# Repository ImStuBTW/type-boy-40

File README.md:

# The Type Boy 40

This keyboard is a test bed for the revised TyepPak Advance microcontroller breakout board. It's a relatively simple 4x12 ortholinear keyboard.

## Features

- TypePak Advance cartridge slot
- VIK expansion port (Bottom mount, requires Type-B FPC cable.)
- Per-key SK6812Mini-E RGB LEDs
- Mid-Mount USB-C port
- Power switch
- Reset button

## Current Status

This board hasn't been built yet. Fab at your own risk!

## BOM

TBD

## Footprint Credits

- `diode-rear` is a variant of the stock Ergogen footprint which only has SMD pads on the rear.
- `esd` is a converted `SOT-23-6_Handsoldering` footprint from KiCAD's stock libraries.
- `fff_logo` is a logo I made. Features SMD pads as glasses.
- `gba` is a converted version of the DS Lite cartridge print from HDR's [Game-Boy-KiCAD-Library](https://github.com/HDR/Game-Boy-KiCad-Library) library.
- `jumper` is a converted KiCAD footprint.
- `led_sk6812mini-e` is from ceoloide's [ergogen-footprints](https://github.com/ceoloide/ergogen-footprints) library.
- `m2mountinghole` is converted from KiCAD.
- `power` is the stock Ergogen slide switch with Pad 3 exposed to allow you to specify which direction of the switch is "on".
- `smd805` is a converted KiCAD hand soldered 805 SMD component footprint.
- `usbcmid` is converted from Keeb.io's [Keebio-Parts.pretty](https://github.com/keebio/Keebio-Parts.pretty) library.
- `vik_cutout` is something I threw together in about 4 minutes.
- `vik_horizontal` and `vik_logo` come from sadekbaroudi's excellent [VIK](https://github.com/sadekbaroudi/vik) keyboard extension standard. Go Fingerpunch!

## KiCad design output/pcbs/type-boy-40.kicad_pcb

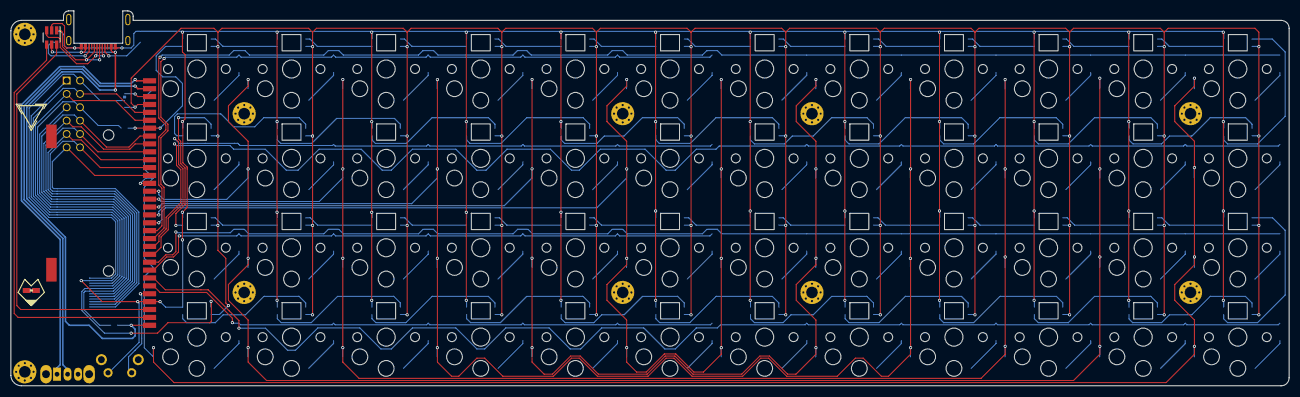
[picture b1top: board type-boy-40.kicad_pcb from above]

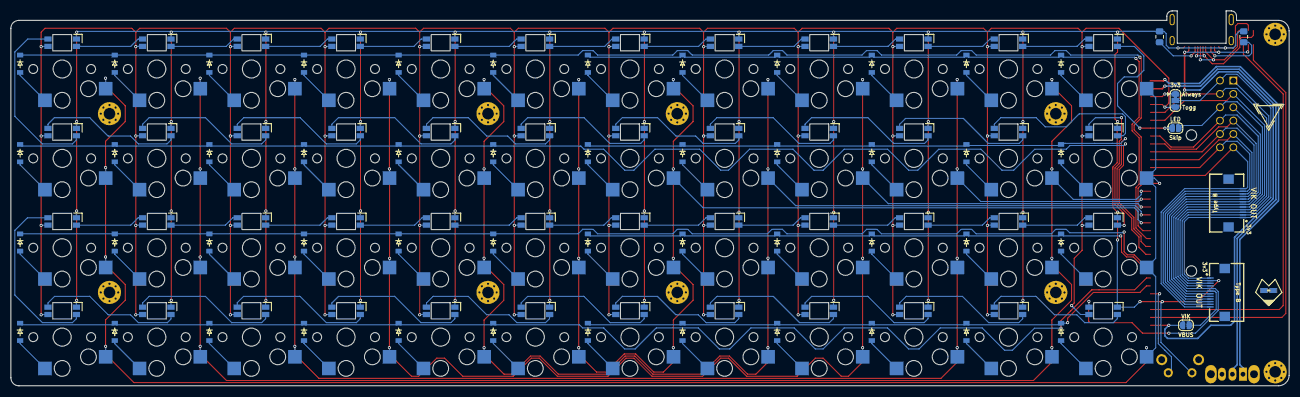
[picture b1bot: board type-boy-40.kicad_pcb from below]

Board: 2 copper layers, 243.1 x 71.3 mm, 161 parts (53 on the bottom side), 122 nets.

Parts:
D1, D2, D3, D4, D5, D6, D7, D8, D9, D10, D11, D12, D13, D14, D15, D16, D17, D18, D19, D20, D21, D22, D23, D24, D25, D26, D27, D28, D29, D30, D31, D32, D33, D34, D35, D36, D37, D38, D39, D40, D41, D42, D43, D44, D45, D46, D47, D48: ComboDiode
LED1, LED2, LED3, LED4, LED5, LED6, LED7, LED8, LED9, LED10, LED11, LED12, LED13, LED14, LED15, LED16, LED17, LED18, LED19, LED20, LED21, LED22, LED23, LED24, LED25, LED26, LED27, LED28, LED29, LED30, LED31, LED32, LED33, LED34, LED35, LED36, LED37, LED38, LED39, LED40, LED41, LED42, LED43, LED44, LED45, LED46, LED47, LED48: led_SK6812mini-e (per-keysingle-side)
S1, S2, S3, S4, S5, S6, S7, S8, S9, S10, S11, S12, S13, S14, S15, S16, S17, S18, S19, S20, S21, S22, S23, S24, S25, S26, S27, S28, S29, S30, S31, S32, S33, S34, S35, S36, S37, S38, S39, S40, S41, S42, S43, S44, S45, S46, S47, S48: PG1350
TH1: vik-keyboard-throughole
VIK OUT: vik-keyboard-connector-horizontal
XX1: vik-keyboard-connector-horizontal
XX3: SolderJumper-3_default.3mm_Bridged12_RoundedPad1.0x1.5mm
XX4: SolderJumper-2_from.3mm_Open_RoundedPad1.0x1.5mm
XX6, XX8: Untitled
_1, _2, _3, _4, _5, _6, _7, _8, _9, _10: MountingHole_2.2mm_M2_Pad_Via

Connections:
GND: LED1.3, LED2.3, LED3.3, LED4.3, LED5.3, LED6.3, LED7.3, LED8.3, LED9.3, LED10.3, LED11.3, LED12.3, LED13.3, LED14.3, LED15.3, LED16.3, LED17.3, LED18.3, LED19.3, LED20.3, LED21.3, LED22.3, LED23.3, LED24.3, LED25.3, LED26.3, LED27.3, LED28.3, LED29.3, LED30.3, LED31.3, LED32.3, LED33.3, LED34.3, LED35.3, LED36.3, LED37.3, LED38.3, LED39.3, LED40.3, LED41.3, LED42.3, LED43.3, LED44.3, LED45.3, LED46.3, LED47.3, LED48.3, TH1.2, VIK OUT.2, XX1.2
LED1: LED4.2, LED8.4
LED2: LED8.2, LED12.4
LED3: LED12.2, LED16.4
LED4: LED16.2, LED20.4
LED5: LED20.2, LED24.4
LED6: LED24.2, LED28.4
LED7: LED28.2, LED32.4
LED8: LED32.2, LED36.4
LED9: LED36.2, LED40.4
LED10: LED40.2, LED44.4
LED11: LED44.2, LED48.4
LED12: LED47.4, LED48.2
LED13: LED43.4, LED47.2
LED14: LED39.4, LED43.2
LED15: LED35.4, LED39.2
LED16: LED31.4, LED35.2
LED17: LED27.4, LED31.2
LED18: LED23.4, LED27.2
LED19: LED19.4, LED23.2
LED20: LED15.4, LED19.2
LED21: LED11.4, LED15.2
LED22: LED7.4, LED11.2
LED23: LED3.4, LED7.2
LED24: LED2.4, LED3.2
LED25: LED2.2, LED6.4
LED26: LED6.2, LED10.4
LED27: LED10.2, LED14.4
LED28: LED14.2, LED18.4
LED29: LED18.2, LED22.4
LED30: LED22.2, LED26.4
LED31: LED26.2, LED30.4
LED32: LED30.2, LED34.4
LED33: LED34.2, LED38.4
LED34: LED38.2, LED42.4
LED35: LED42.2, LED46.4
LED36: LED45.4, LED46.2
LED37: LED41.4, LED45.2
LED38: LED37.4, LED41.2
LED39: LED33.4, LED37.2
LED40: LED29.4, LED33.2
LED41: LED25.4, LED29.2
LED42: LED21.4, LED25.2
LED43: LED17.4, LED21.2
LED44: LED13.4, LED17.2
LED45: LED9.4, LED13.2
LED46: LED5.4, LED9.2
LED47: LED1.4, LED5.2
LED48: LED1.2, TH1.5, VIK OUT.5, XX1.5
MISO: TH1.11, VIK OUT.11, XX1.11
MOSI: TH1.8, VIK OUT.8, XX1.8
SCK: TH1.12, VIK OUT.12, XX1.12
SCL: TH1.4, VIK OUT.4, XX1.4
SDA: TH1.3, VIK OUT.3, XX1.3
V33_JUMPER: TH1.1, VIK OUT.1, XX1.1, XX3.2
V33_TOGG: LED1.1, LED2.1, LED3.1, LED4.1, LED5.1, LED6.1, LED7.1, LED8.1, LED9.1, LED10.1, LED11.1, LED12.1, LED13.1, LED14.1, LED15.1, LED16.1, LED17.1, LED18.1, LED19.1, LED20.1, LED21.1, LED22.1, LED23.1, LED24.1, LED25.1, LED26.1, LED27.1, LED28.1, LED29.1, LED30.1, LED31.1, LED32.1, LED33.1, LED34.1, LED35.1, LED36.1, LED37.1, LED38.1, LED39.1, LED40.1, LED41.1, LED42.1, LED43.1, LED44.1, LED45.1, LED46.1, LED47.1, LED48.1, XX3.3
VIK_CS: TH1.10, VIK OUT.10, XX1.10
VIK_GPIO1: TH1.7, VIK OUT.7, XX1.7
VIK_GPIO2: TH1.9, VIK OUT.9, XX1.9
VIK_VBUS: TH1.6, VIK OUT.6, XX1.6, XX4.2
col1: S1.2, S2.2, S3.2, S4.2, S45.2, S46.2, S47.2, S48.2
col2: S5.2, S6.2, S7.2, S8.2, S41.2, S42.2, S43.2, S44.2
col3: S9.2, S10.2, S11.2, S12.2, S37.2, S38.2, S39.2, S40.2
col4: S13.2, S14.2, S15.2, S16.2, S33.2, S34.2, S35.2, S36.2
col5: S17.2, S18.2, S19.2, S20.2, S29.2, S30.2, S31.2, S32.2
col6: S21.2, S22.2, S23.2, S24.2, S25.2, S26.2, S27.2, S28.2
eight_bottom: D30.2, S30.1
eight_home: D31.2, S31.1
eight_mod: D29.2, S29.1
eight_top: D32.2, S32.1
eleven_bottom: D42.2, S42.1
eleven_home: D43.2, S43.1
eleven_mod: D41.2, S41.1
eleven_top: D44.2, S44.1
five_bottom: D18.2, S18.1
five_home: D19.2, S19.1
five_mod: D17.2, S17.1
five_top: D20.2, S20.1
four_bottom: D14.2, S14.1
four_home: D15.2, S15.1
four_mod: D13.2, S13.1
four_top: D16.2, S16.1
nine_bottom: D34.2, S34.1
nine_home: D35.2, S35.1
nine_mod: D33.2, S33.1
nine_top: D36.2, S36.1
one_bottom: D2.2, S2.1
one_home: D3.2, S3.1
one_mod: D1.2, S1.1
one_top: D4.2, S4.1
row1: D1.1, D5.1, D9.1, D13.1, D17.1, D21.1
row2: D2.1, D6.1, D10.1, D14.1, D18.1, D22.1
row3: D3.1, D7.1, D11.1, D15.1, D19.1, D23.1
row4: D4.1, D8.1, D12.1, D16.1, D20.1, D24.1
row5: D25.1, D29.1, D33.1, D37.1, D41.1, D45.1
row6: D26.1, D30.1, D34.1, D38.1, D42.1, D46.1
row7: D27.1, D31.1, D35.1, D39.1, D43.1, D47.1
row8: D28.1, D32.1, D36.1, D40.1, D44.1, D48.1
seven_bottom: D26.2, S26.1
seven_home: D27.2, S27.1
seven_mod: D25.2, S25.1
seven_top: D28.2, S28.1
six_bottom: D22.2, S22.1
six_home: D23.2, S23.1
six_mod: D21.2, S21.1
six_top: D24.2, S24.1
ten_bottom: D38.2, S38.1
ten_home: D39.2, S39.1
ten_mod: D37.2, S37.1
ten_top: D40.2, S40.1
three_bottom: D10.2, S10.1
three_home: D11.2, S11.1
three_mod: D9.2, S9.1
three_top: D12.2, S12.1
twelve_bottom: D46.2, S46.1
twelve_home: D47.2, S47.1
twelve_mod: D45.2, S45.1
twelve_top: D48.2, S48.1
two_bottom: D6.2, S6.1
two_home: D7.2, S7.1
two_mod: D5.2, S5.1
two_top: D8.2, S8.1

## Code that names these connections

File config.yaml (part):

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          shift: [(1cx-2.75)*-1-nudge+1.25, 0.5cy]
          rotate: 90
        params:
          KB_GPIO1: row1
          KB_GPIO2: row5
          KB_GPIO3: row2
          KB_GPIO4: row6
          KB_GPIO5: row3
          KB_GPIO6: row7
          KB_GPIO7: row4
          KB_GPIO8: row8
          KB_GPIO9: col6
          KB_GPIO10: col5
          KB_GPIO11: col4
          KB_GPIO12: col3
          KB_GPIO13: col2
          KB_GPIO14: col1
      # Mid-mount USB-C port.
      # Wires up to USB pins coming from GBA cart.
      usbc:
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          VIK4: SCL
          VIK5: LED48
          VIK6: VIK_VBUS
          VIK7: VIK_GPIO1
          VIK8: MOSI
          VIK9: VIK_GPIO2
          VIK10: VIK_CS
          VIK11: MISO
          VIK12: SCK
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          VIK4: SCL
          VIK5: LED48
          VIK6: VIK_VBUS
          VIK7: VIK_GPIO1
          VIK8: MOSI
          VIK9: VIK_GPIO2
          VIK10: VIK_CS
          VIK11: MISO
          VIK12: SCK
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          VIK4: SCL
          VIK5: LED48
          VIK6: VBUS
          VIK7: VIK_GPIO1
          VIK8: MOSI
          VIK9: VIK_GPIO2
          VIK10: VIK_CS
          VIK11: MISO
          VIK12: SCK
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
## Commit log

2025-07-06 Added PCB image to README.
2025-07-06 Fixed typo.
2025-08-23 Moved TypePak to left side.
2025-08-27 Updated Image.
